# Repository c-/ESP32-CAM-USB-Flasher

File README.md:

# ESP32-CAM-USB-Flasher

Just a simple adapter for an ESP32-CAM to provide USB power/comms and allow
for easy flashing.

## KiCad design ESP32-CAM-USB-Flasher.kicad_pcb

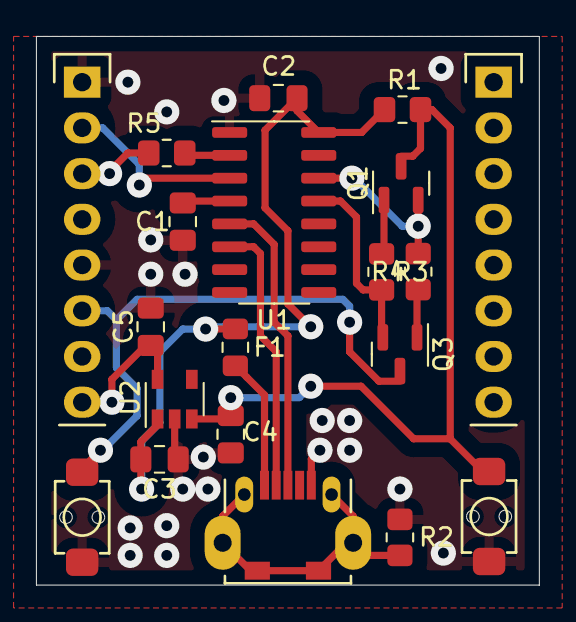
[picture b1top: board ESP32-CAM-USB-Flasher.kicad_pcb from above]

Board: 2 copper layers, 27.9 x 30.5 mm, 20 parts (0 on the bottom side), 17 nets.

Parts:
C1, C2, C4: 100n; C_0805_2012Metric_Pad1.18x1.45mm_HandSolder
C3: 10u; C_0805_2012Metric_Pad1.18x1.45mm_HandSolder
C5: 22u; C_0805_2012Metric_Pad1.18x1.45mm_HandSolder
F1: 500mA; Fuse_0805_2012Metric_Pad1.15x1.40mm_HandSolder
J1: LEFT; Socket_Strip_Straight_1x08_nograf
J2: USB_B_Micro; USB_Micro-B_CNC_C10418
J3: RIGHT; Socket_Strip_Straight_1x08_nograf
Q1, Q3: S8050; SOT-23
R1, R3, R4: 10K; R_0805_2012Metric_Pad1.20x1.40mm_HandSolder
R2: 1M; R_0805_2012Metric_Pad1.20x1.40mm_HandSolder
R5: 470R; R_0805_2012Metric_Pad1.20x1.40mm_HandSolder
SW1: RESET; SW_Tact_C354947
SW2: FLASH; SW_Tact_C354947
U1: CH340C; SOIC-16_3.9x9.9mm_P1.27mm
U2: ME6217; SOT-23-5

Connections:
+3V3: C5.1, J1.8, U2.5 (VOUT)
+5V: C2.1, C3.1, F1.1, R1.1, U1.16 (VCC), U2.1 (VIN)
/CHTX: R5.2, U1.2 (TXD)
/D+: J2.3 (D+), U1.5 (UD+)
/D-: J2.2 (D-), U1.6 (UD-)
/DTR: Q3.2 (E), R3.1, U1.13 (~DTR)
/EN: C4.1, Q1.3 (C), R1.2, SW1.1, U2.3 (CE)
/GPIO0: J1.6, Q3.3 (C), SW2.1
/RTS: Q1.2 (E), R4.2, U1.14 (~RTS)
/URXD: J1.3, R5.1
/UTXD: J1.2, U1.3 (RXD)
GND: C1.1, C2.2, C3.2, C4.2, C5.2, J1.1, J1.5, J2.5 (GND), J3.7, R2.1, SW1.2, SW2.2, U1.1 (GND), U2.2 (VSS)
unnamed: F1.2, J2.1 (VBUS)
unnamed: J2.6 (Shield), R2.2
unnamed: Q1.1 (B), R3.2
unnamed: Q3.1 (B), R4.1
unnamed: C1.2, U1.4 (V3)

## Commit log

2021-08-14 another rev
2022-12-26 get the transistor footprint right
2022-12-26 add some docs
2022-12-26 PDF schematic
2022-12-26 a better photo collage
